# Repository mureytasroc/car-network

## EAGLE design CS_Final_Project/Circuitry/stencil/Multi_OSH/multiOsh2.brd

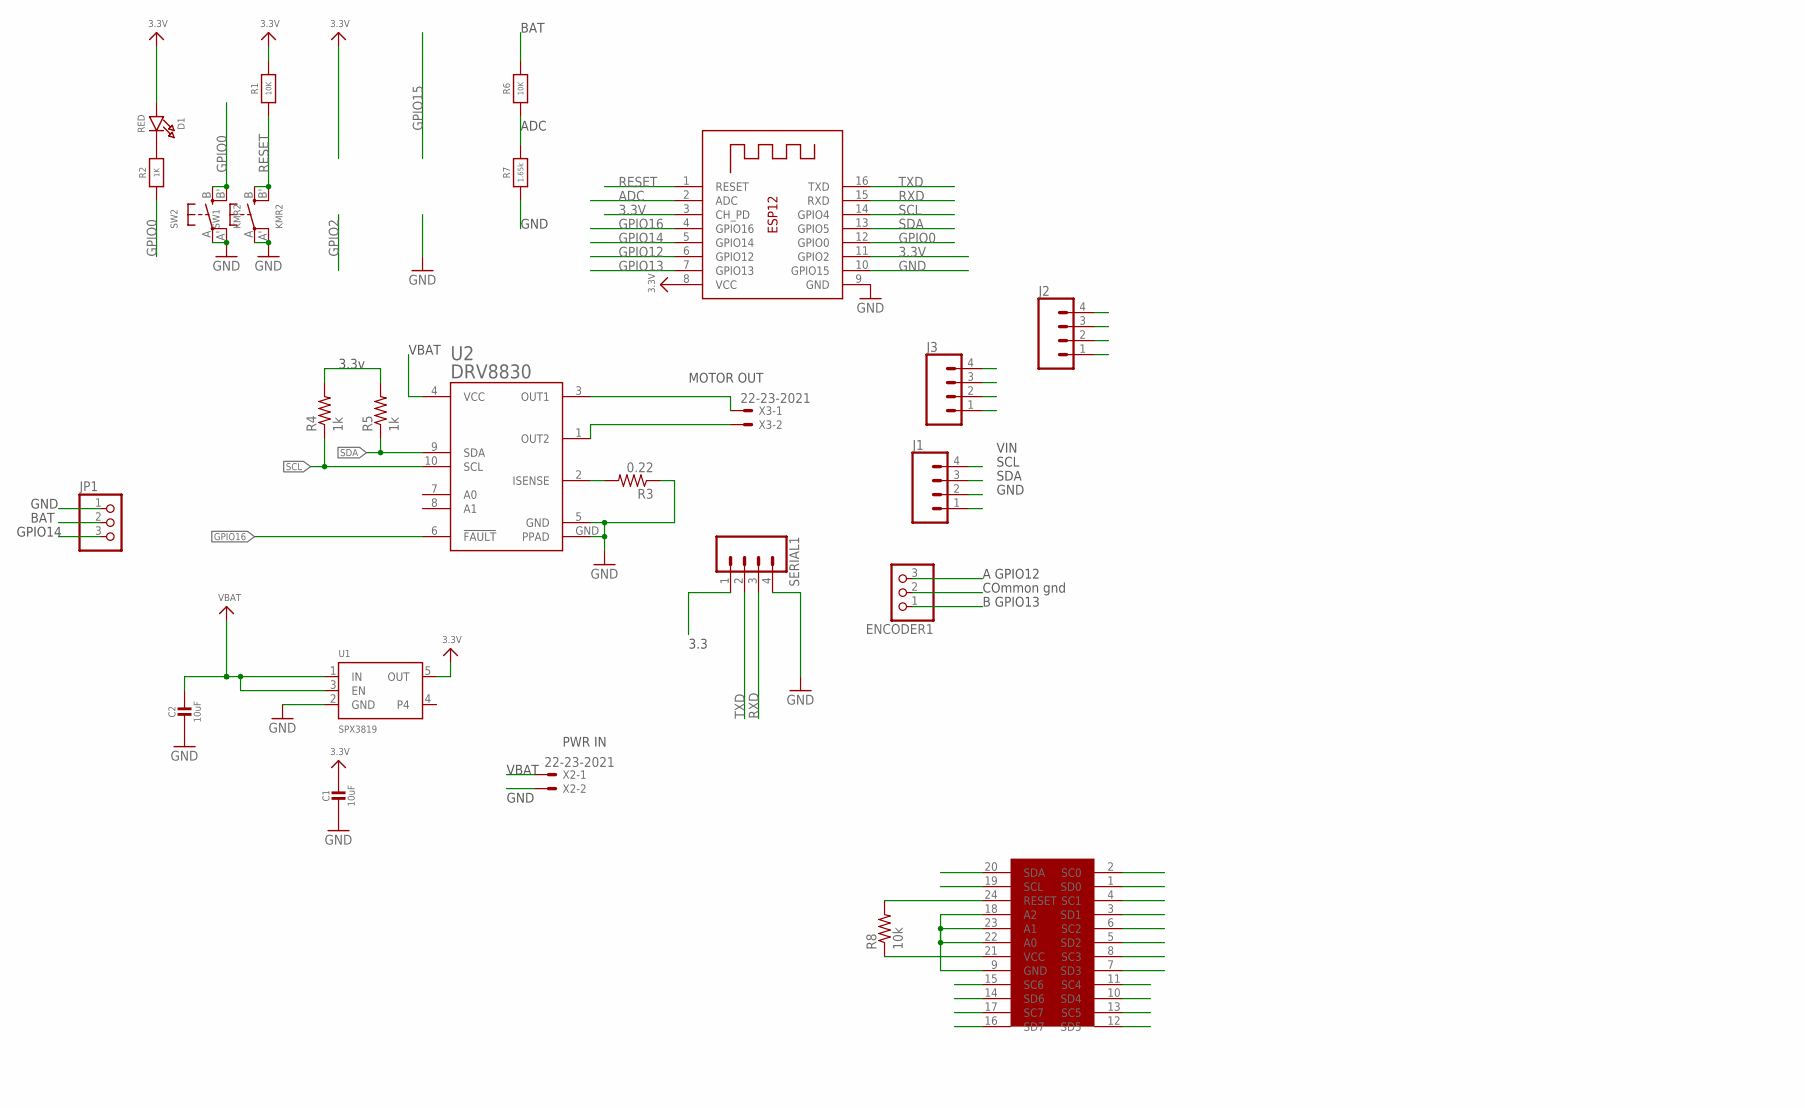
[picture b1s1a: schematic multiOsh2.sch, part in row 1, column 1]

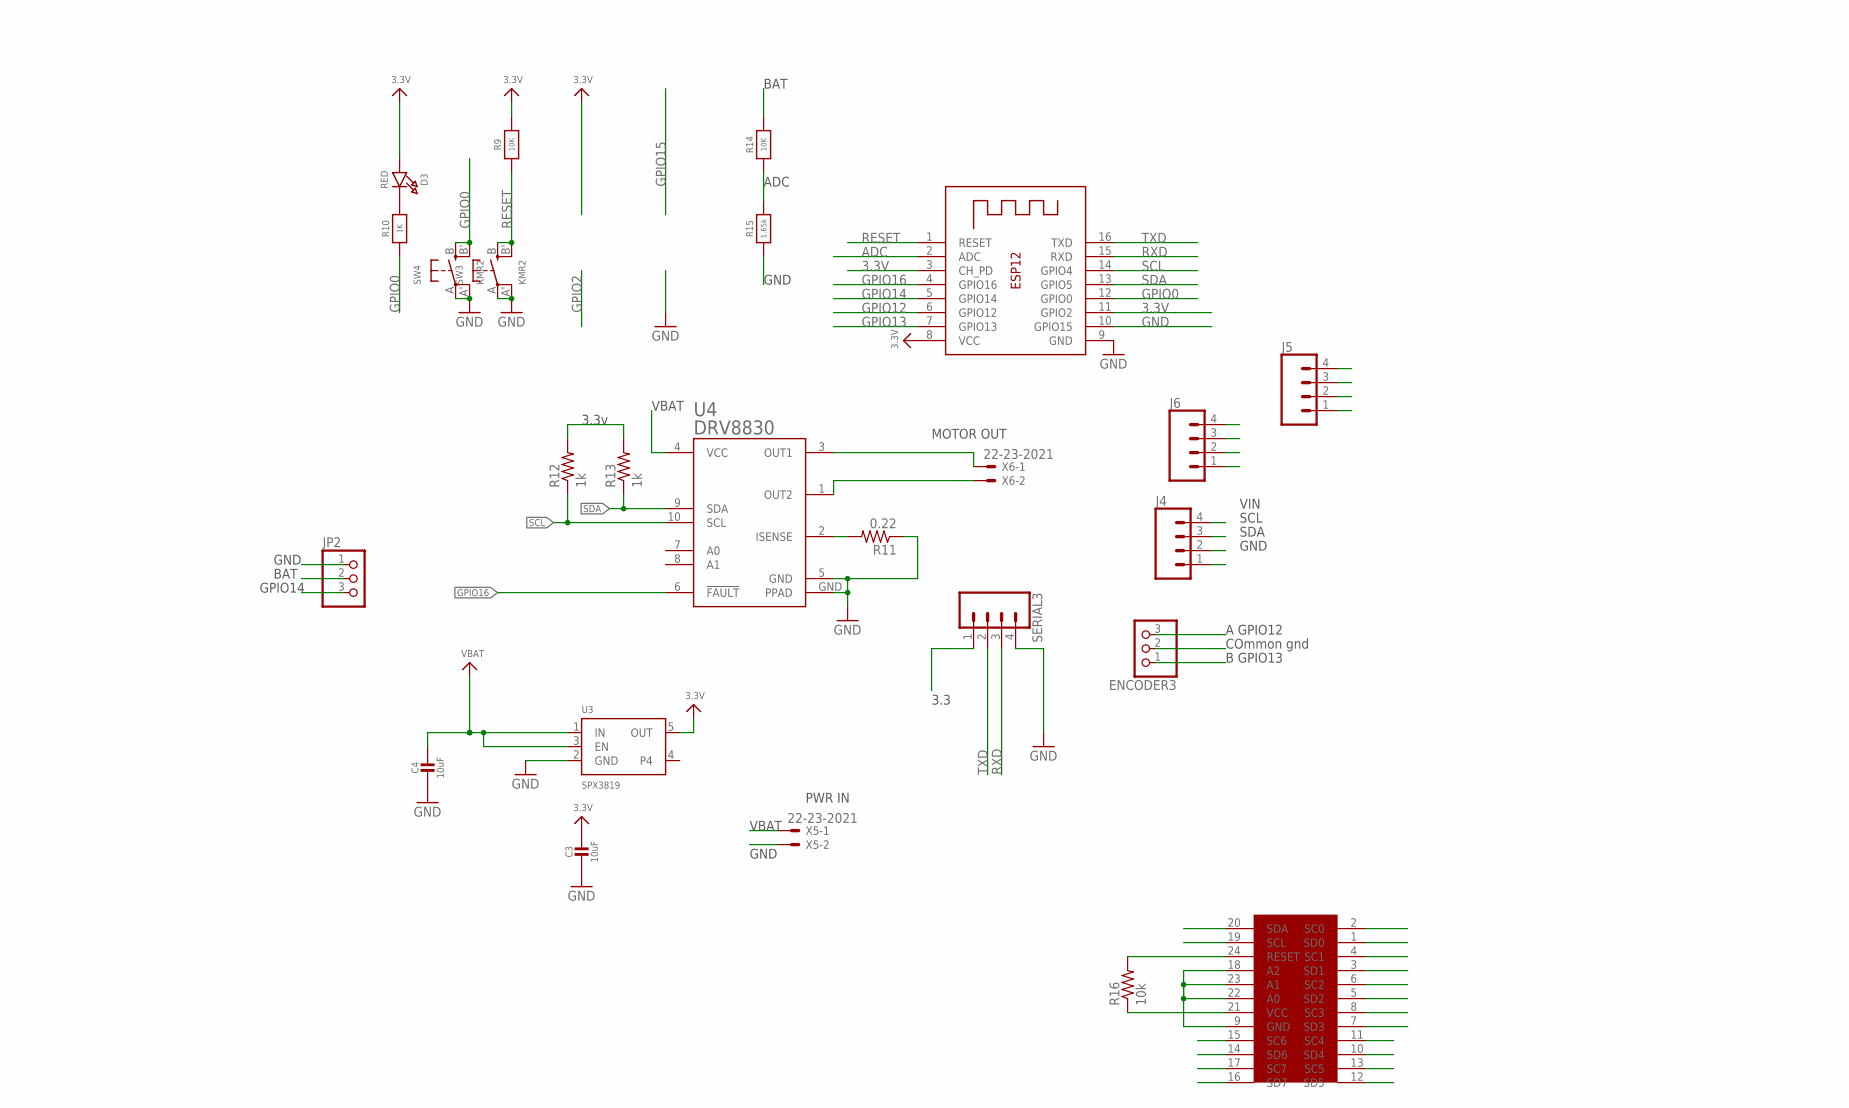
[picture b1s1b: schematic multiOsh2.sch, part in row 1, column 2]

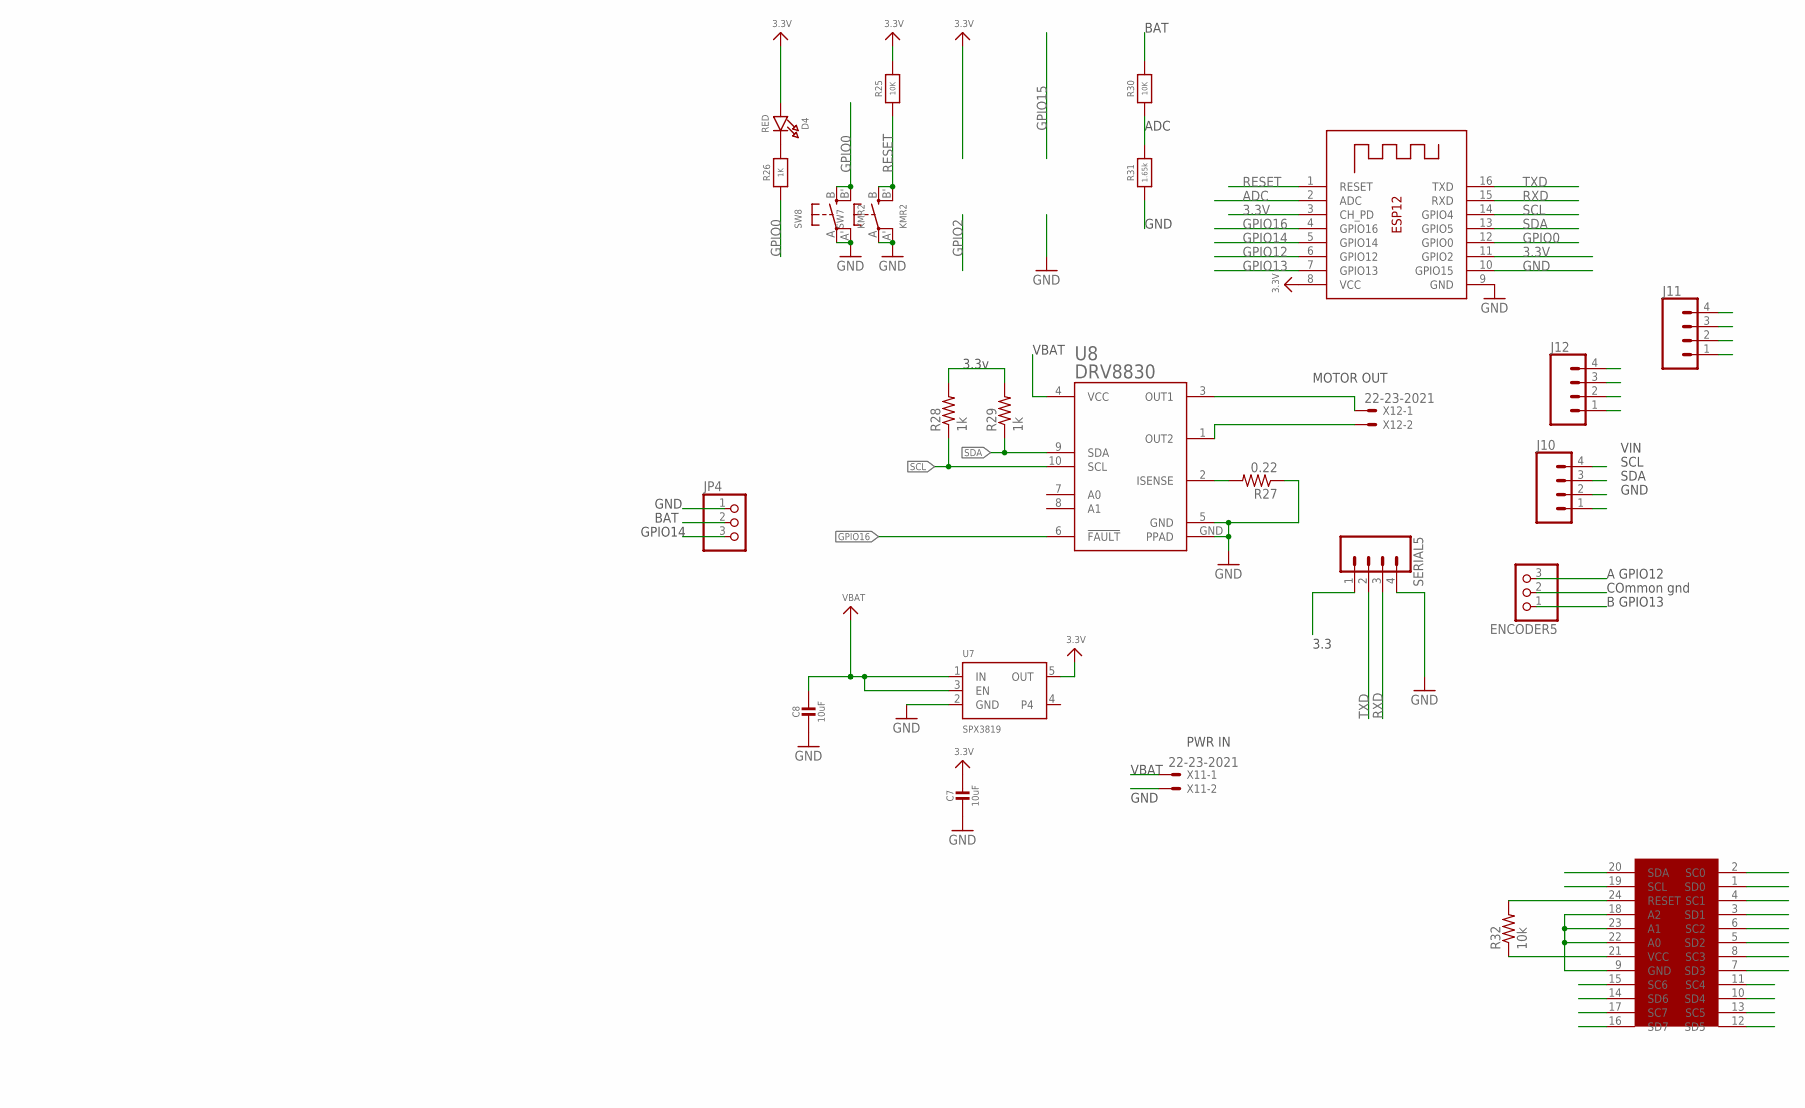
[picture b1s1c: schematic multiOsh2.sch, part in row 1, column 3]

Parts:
C1, C2, C3, C4, C7, C8: 10uF; 0805-NO
D1, D3, D4: RED; CHIPLED_0805_NOOUTLINE
ENCODER1, ENCODER3, ENCODER5: PINHD-1X3; 1X03
J1, J2, J3, J4, J5, J6, J10, J11, J12: CONN_04; 1X04
JP1, JP2, JP4: PINHD-1X3; 1X03
R1, R6, R9, R14, R25, R30: 10K; 0805-NO
R2, R10, R26: 1K; 0805-NO
R3, R11, R27: 0.22; 0805
R4, R5, R12, R13, R28, R29: 1k; R0805
R7, R15, R31: 1.65k; 0805-NO
R8, R16, R32: 10k; M0805
SERIAL1, SERIAL3, SERIAL5: CONN_04; 1X04
SW1, SW2, SW3, SW4, SW7, SW8: KMR2; BTN_KMR2_4.6X2.8
U1, U3, U7: SPX3819; SOT23-5
U2, U4, U8: DRV8830; MSOP-10-GNDPAD
U$8, U$16, U$35: TCA9548A; QFN24-4X4
X1, X4, X10: ESP-12
X2, X3, X5, X6, X11, X12: 22-23-2021

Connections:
3.3V: C1.1, C3.1, C7.1, D1.A, D3.A, D4.A, J1.4, J2.4, J3.4, J4.4, J5.4, J6.4, J10.4, J11.4, J12.4, R1.2, R4.2, R5.2, R8.1, R9.2, R12.2, R13.2, R16.1, R25.2, R28.2, R29.2, R32.1, SERIAL1.1, SERIAL3.1, SERIAL5.1, U1.5 (OUT), U3.5 (OUT), U7.5 (OUT), U$8.21 (VCC), U$16.21 (VCC), U$35.21 (VCC), X1.3 (CH_PD), X1.8 (VCC), X1.11 (GPIO2), X4.3 (CH_PD), X4.8 (VCC), X4.11 (GPIO2), X10.3 (CH_PD), X10.8 (VCC), X10.11 (GPIO2)
ADC: R6.1, R7.2, R14.1, R15.2, R30.1, R31.2, X1.2 (ADC), X4.2 (ADC), X10.2 (ADC)
GND: C1.2, C2.2, C3.2, C4.2, C7.2, C8.2, ENCODER1.2, ENCODER3.2, ENCODER5.2, J1.1, J2.1, J3.1, J4.1, J5.1, J6.1, J10.1, J11.1, J12.1, JP1.1, JP2.1, JP4.1, R3.1, R7.1, R11.1, R15.1, R27.1, R31.1, SERIAL1.4, SERIAL3.4, SERIAL5.4, SW1.A, SW1.A' (P1), SW2.A, SW2.A' (P1), SW3.A, SW3.A' (P1), SW4.A, SW4.A' (P1), SW7.A, SW7.A' (P1), SW8.A, SW8.A' (P1), U1.2 (GND), U2.5 (GND), U2.GND (PPAD), U3.2 (GND), U4.5 (GND), U4.GND (PPAD), U7.2 (GND), U8.5 (GND), U8.GND (PPAD), U$8.9 (GND), U$8.18 (A2), U$8.22 (A0), U$8.23 (A1), U$16.9 (GND), U$16.18 (A2), U$16.22 (A0), U$16.23 (A1), U$35.9 (GND), U$35.18 (A2), U$35.22 (A0), U$35.23 (A1), X1.9 (GND), X1.10 (GPIO15), X2.2, X4.9 (GND), X4.10 (GPIO15), X5.2, X10.9 (GND), X10.10 (GPIO15), X11.2
GPIO0: R2.1, R10.1, R26.1, SW2.B (S), SW2.B' (S1), SW4.B (S), SW4.B' (S1), SW8.B (S), SW8.B' (S1), X1.12 (GPIO0), X4.12 (GPIO0), X10.12 (GPIO0)
GPIO12: ENCODER1.3, ENCODER3.3, ENCODER5.3, X1.6 (GPIO12), X4.6 (GPIO12), X10.6 (GPIO12)
GPIO13: ENCODER1.1, ENCODER3.1, ENCODER5.1, X1.7 (GPIO13), X4.7 (GPIO13), X10.7 (GPIO13)
GPIO14: JP1.3, JP2.3, JP4.3, X1.5 (GPIO14), X4.5 (GPIO14), X10.5 (GPIO14)
GPIO16: U2.6 (!FAULT), U4.6 (!FAULT), U8.6 (!FAULT), X1.4 (GPIO16), X4.4 (GPIO16), X10.4 (GPIO16)
MOT1: U2.1 (OUT2), X3.2
MOT2: U2.3 (OUT1), X3.1
MOT3: U4.1 (OUT2), X6.2
MOT4: U4.3 (OUT1), X6.1
MOT7: U8.1 (OUT2), X12.2
MOT8: U8.3 (OUT1), X12.1
unnamed: D1.C, R2.2
unnamed: R3.2, U2.2 (ISENSE)
unnamed: R8.2, U$8.24 (RESET)
unnamed: D3.C, R10.2
unnamed: R11.2, U4.2 (ISENSE)
unnamed: R16.2, U$16.24 (RESET)
unnamed: D4.C, R26.2
unnamed: R27.2, U8.2 (ISENSE)
unnamed: R32.2, U$35.24 (RESET)
RESET: R1.1, R9.1, R25.1, SW1.B (S), SW1.B' (S1), SW3.B (S), SW3.B' (S1), SW7.B (S), SW7.B' (S1), X1.1 (RESET), X4.1 (RESET), X10.1 (RESET)
RXD: SERIAL1.3, SERIAL3.3, SERIAL5.3, X1.15 (RXD), X4.15 (RXD), X10.15 (RXD)
SC1: U$8.2 (SC0)
SC2: U$8.4 (SC1)
SC3: U$8.6 (SC2)
SC4: J3.2, U$8.8 (SC3)
SC5: J1.2, U$8.15 (SC6)
SC6: U$8.17 (SC7)
SC7: U$8.11 (SC4)
SC8: J2.2, U$8.13 (SC5)
SC9: U$16.2 (SC0)
SC10: U$16.4 (SC1)
SC11: U$16.6 (SC2)
SC12: J6.2, U$16.8 (SC3)
SC13: J4.2, U$16.15 (SC6)
SC14: U$16.17 (SC7)
SC15: U$16.11 (SC4)
SC24: J5.2, U$16.13 (SC5)
SC25: U$35.2 (SC0)
SC26: U$35.4 (SC1)
SC27: U$35.6 (SC2)
SC28: J12.2, U$35.8 (SC3)
SC29: J10.2, U$35.15 (SC6)
SC30: U$35.17 (SC7)
SC31: U$35.11 (SC4)
SC40: J11.2, U$35.13 (SC5)
SCL: R4.1, R12.1, R28.1, U2.10 (SCL), U4.10 (SCL), U8.10 (SCL), U$8.19 (SCL), U$16.19 (SCL), U$35.19 (SCL), X1.14 (GPIO4), X4.14 (GPIO4), X10.14 (GPIO4)
SD1: U$8.1 (SD0)
SD2: U$8.3 (SD1)
SD3: U$8.5 (SD2)
SD4: J3.3, U$8.7 (SD3)
SD5: J1.3, U$8.14 (SD6)
SD6: U$8.16 (SD7)
SD7: U$8.10 (SD4)
SD8: J2.3, U$8.12 (SD5)
SD9: U$16.1 (SD0)
SD10: U$16.3 (SD1)
SD11: U$16.5 (SD2)
SD12: J6.3, U$16.7 (SD3)
SD13: J4.3, U$16.14 (SD6)
SD14: U$16.16 (SD7)
SD15: U$16.10 (SD4)
SD24: J5.3, U$16.12 (SD5)
SD25: U$35.1 (SD0)
SD26: U$35.3 (SD1)
SD27: U$35.5 (SD2)
SD28: J12.3, U$35.7 (SD3)
SD29: J10.3, U$35.14 (SD6)
SD30: U$35.16 (SD7)
SD31: U$35.10 (SD4)
SD40: J11.3, U$35.12 (SD5)
SDA: R5.1, R13.1, R29.1, U2.9 (SDA), U4.9 (SDA), U8.9 (SDA), U$8.20 (SDA), U$16.20 (SDA), U$35.20 (SDA), X1.13 (GPIO5), X4.13 (GPIO5), X10.13 (GPIO5)
TXD: SERIAL1.2, SERIAL3.2, SERIAL5.2, X1.16 (TXD), X4.16 (TXD), X10.16 (TXD)
VBAT: C2.1, C4.1, C8.1, JP1.2, JP2.2, JP4.2, R6.2, R14.2, R30.2, U1.1 (IN), U1.3 (EN), U2.4 (VCC), U3.1 (IN), U3.3 (EN), U4.4 (VCC), U7.1 (IN), U7.3 (EN), U8.4 (VCC), X2.1, X5.1, X11.1

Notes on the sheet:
3.3v
VBAT
BAT
GND
ADC
PWR IN
MOTOR OUT
GPIO14
VIN
SCL
SDA
COmmon gnd
A GPIO12
B GPIO13
3.3

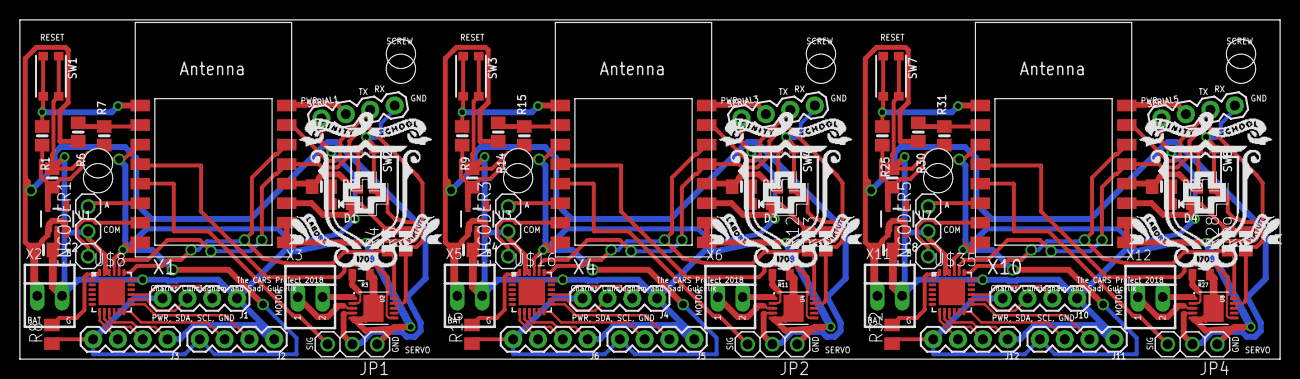
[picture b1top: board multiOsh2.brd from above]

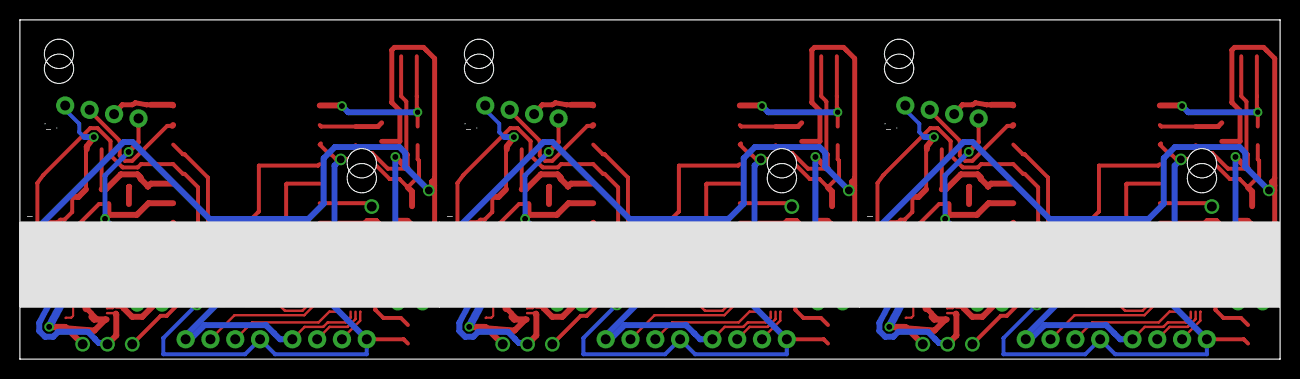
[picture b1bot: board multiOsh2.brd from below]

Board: 2 copper layers, 129.0 x 34.7 mm, 84 parts (6 on the bottom side), 47 nets.

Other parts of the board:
U$36, U$39, U$42: HUZZAHLOGO
U$37, U$40, U$43: ADAFRUIT_TEXT_20MM
U$38, U$41, U$44: TRIN

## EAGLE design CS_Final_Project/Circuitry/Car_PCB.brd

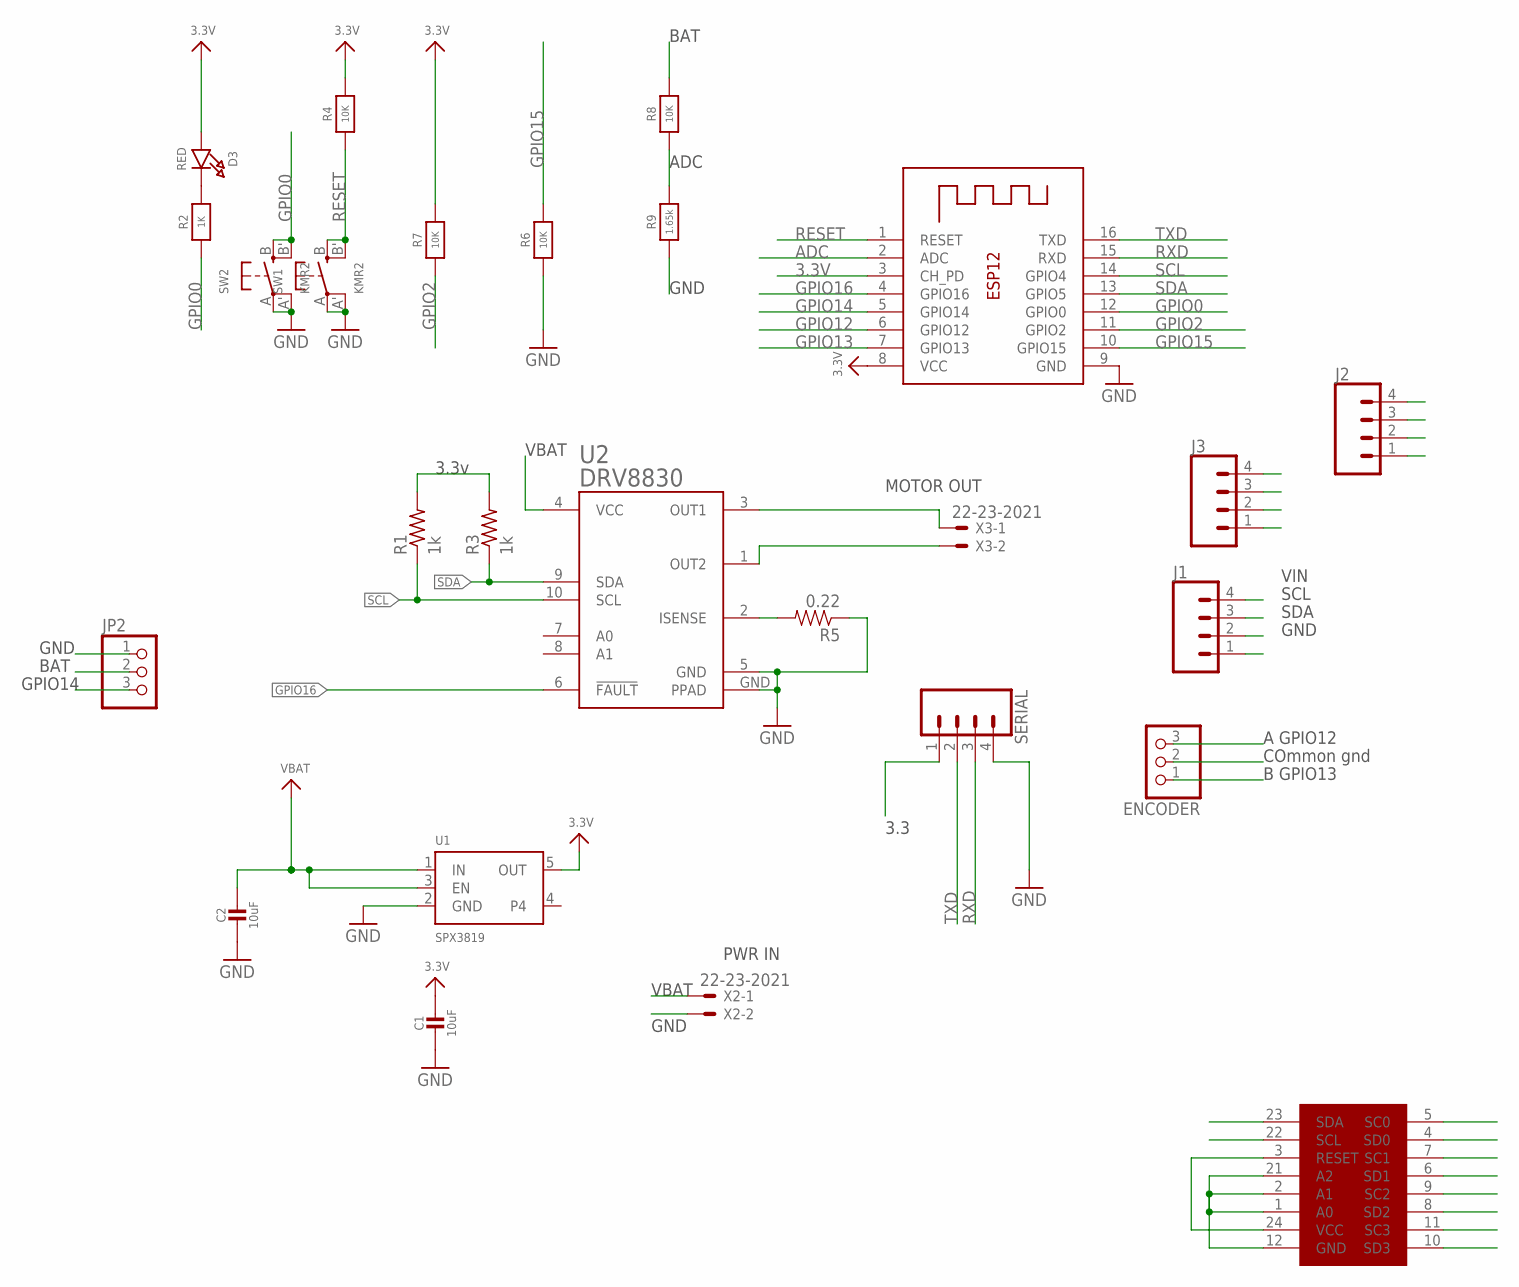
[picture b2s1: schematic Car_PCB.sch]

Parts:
C1, C2: 10uF; 0805-NO
D3: RED; CHIPLED_0805_NOOUTLINE
ENCODER: PINHD-1X3; 1X03
J1, J2, J3: CONN_04; 1X04
JP2: PINHD-1X3; 1X03
R1, R3: 1k; R0805
R2: 1K; 0805-NO
R4, R6, R7, R8: 10K; 0805-NO
R5: 0.22; 0805
R9: 1.65k; 0805-NO
SERIAL: CONN_04; 1X04
SW1, SW2: KMR2; BTN_KMR2_4.6X2.8
U1: SPX3819; SOT23-5
U2: DRV8830; MSOP-10-GNDPAD
U$1: TCA9548A; QFN24-4X4
X1: ESP-12
X2, X3: 22-23-2021

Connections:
3.3V: C1.1, D3.A, J1.4, J2.4, J3.4, R1.2, R3.2, R4.2, R7.2, SERIAL.1, U1.5 (OUT), U$1.3 (RESET), U$1.24 (VCC), X1.3 (CH_PD), X1.8 (VCC)
ADC: R8.1, R9.2, X1.2 (ADC)
GND: C1.2, C2.2, ENCODER.2, J1.1, J2.1, J3.1, JP2.1, R5.1, R6.1, R9.1, SERIAL.4, SW1.A, SW1.A' (P1), SW2.A, SW2.A' (P1), U1.2 (GND), U2.5 (GND), U2.GND (PPAD), U$1.1 (A0), U$1.2 (A1), U$1.12 (GND), U$1.21 (A2), X1.9 (GND), X2.2
GPIO0: R2.1, SW2.B (S), SW2.B' (S1), X1.12 (GPIO0)
GPIO2: R7.1, X1.11 (GPIO2)
GPIO12: ENCODER.3, X1.6 (GPIO12)
GPIO13: ENCODER.1, X1.7 (GPIO13)
GPIO14: JP2.3, X1.5 (GPIO14)
GPIO15: R6.2, X1.10 (GPIO15)
GPIO16: U2.6 (!FAULT), X1.4 (GPIO16)
MOT1: U2.3 (OUT1), X3.1
MOT2: U2.1 (OUT2), X3.2
unnamed: D3.C, R2.2
unnamed: R5.2, U2.2 (ISENSE)
RESET: R4.1, SW1.B (S), SW1.B' (S1), X1.1 (RESET)
RXD: SERIAL.3, X1.15 (RXD)
SC0: J1.3, U$1.5 (SC0)
SC1: J2.3, U$1.7 (SC1)
SC2: U$1.9 (SC2)
SC3: J3.3, U$1.11 (SC3)
SCL: R1.1, U2.10 (SCL), U$1.22 (SCL), X1.14 (GPIO4)
SD0: J1.2, U$1.4 (SD0)
SD1: J2.2, U$1.6 (SD1)
SD2: U$1.8 (SD2)
SD3: J3.2, U$1.10 (SD3)
SDA: R3.1, U2.9 (SDA), U$1.23 (SDA), X1.13 (GPIO5)
TXD: SERIAL.2, X1.16 (TXD)
VBAT: C2.1, JP2.2, R8.2, U1.1 (IN), U1.3 (EN), U2.4 (VCC), X2.1

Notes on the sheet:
3.3v
VBAT
BAT
GND
ADC
PWR IN
MOTOR OUT
GPIO14
VIN
SCL
SDA
COmmon gnd
A GPIO12
B GPIO13
3.3

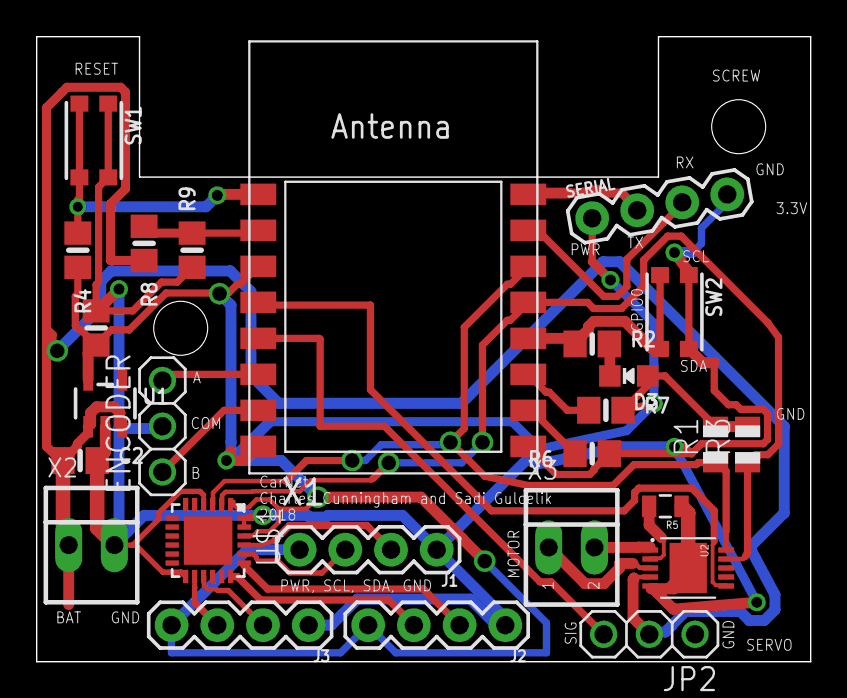
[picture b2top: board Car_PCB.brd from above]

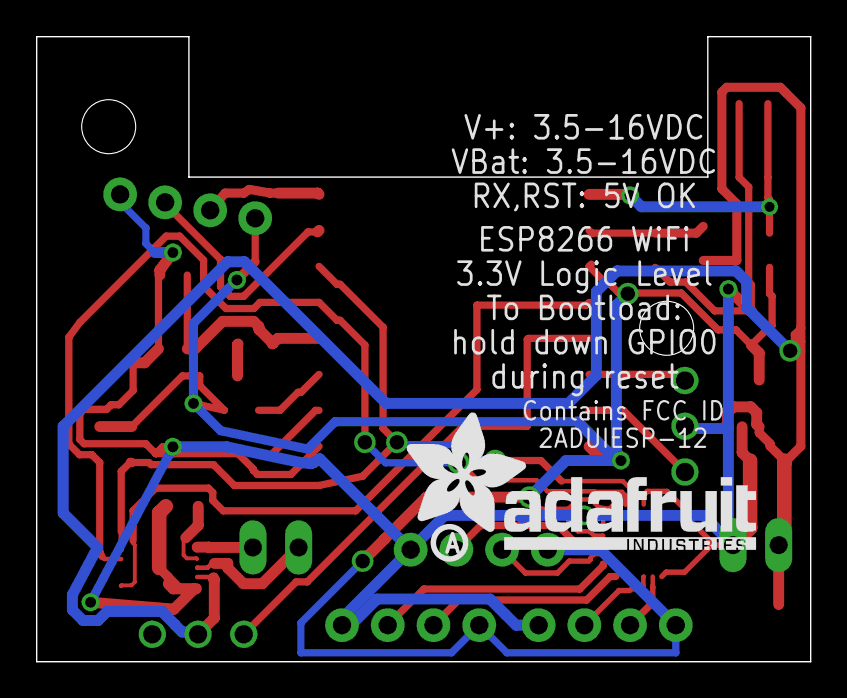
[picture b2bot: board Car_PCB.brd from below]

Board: 2 copper layers, 43.0 x 34.7 mm, 29 parts (3 on the bottom side), 26 nets.

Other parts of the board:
U$2: HUZZAHLOGO
U$12: ADAFRUIT_TEXT_20MM
U$13: PCBFEAT-REV-040

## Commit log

2018-04-25 init
2018-05-17 Revert "Merge branch 'master' of https://github.com/mureytasroc/CarNetwork"
    This reverts commit a45a0045a92c6dc43e66f74dc99afbd22e46fa88, reversing
    changes made to 7d7a9c1b56f2fe83920f8a54f55361a334df6815.
2018-05-22 now?
2018-05-24 trying
2018-05-31 kaka
2018-06-04 midFixing
2018-06-04 fsadjk
2018-06-04 adfs
2018-06-04 final edits for a bit
2018-06-05 fdsa
2018-06-05 almostDeBugged
2018-06-05 ITISBEINGIMPLEMENTED
2018-06-05 sadf
2018-06-05 asdf
2018-06-05 dfas
2018-06-05 ItCompilesButIdkWtfIsGoingOn
2018-06-06 doesItWork???
2018-06-06 arrrgghhhhh
2018-06-06 aqzswxdec
2018-06-06 infiniteLoopError
2018-06-06 asdfasdfafsd
2018-06-06 PUUUUSHHHH
2018-06-06 whyDoesItNotWork
2018-06-06 Teleportation
2018-06-06 as;dkasdf;;asfddfsa;adfsadfs;fsadasdfjklafdsjkadfjksk;adfsjsdfa;sadf;
2018-06-06 still#$%^^&***&%
2018-06-07 asffsd
2018-06-07 safdas
2018-06-07 dsaf
2018-06-07 hljkhkl
2018-06-07 gahhhhhhhhhhh!@#$%^%$#@!~!@#$%^%$#@!@#$%^%$#@!@#$%^%$#@!@#$%^%$#@!@#$%$#@#$%$#@#$%$#@!@#$%^$#@#$%^$#@#$%$#@#$%
2018-06-09 master
2018-06-10 T^&BBT^&*B^*&%^R&
2018-06-13 R*%UBNIN
2018-06-13 Revert "a"
    This reverts commit 0ea7e428ac573384afb96676350230cbd42f0eb4.
2018-06-13 Revert "R*%UBNIN"
    This reverts commit 1c2c4b22cea6128684b4be3c85eba9b46d263418.
2018-06-13 Revert "Revert "R*%UBNIN""
    This reverts commit 9cf39a6a1837bb21f0977229fe0c6344483a6f06.
2018-06-13 prakata
2018-06-13 Revert "m"
    This reverts commit 2f721b070915a0c6e64a1e2351bcc087f2a0364c.
2018-06-13 revert
2018-06-13 Revert "fdsa"
    This reverts commit 60add33f88e891808d7423621e5aaa4d47b19a9a.
2018-06-14 Revert "v"
    This reverts commit 7ead5e88b0f2380e4285c9c24e80ec21ea90fb63.
2018-06-15 test
2018-06-16 Doesn't_work_yet

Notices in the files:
parts and their libraries:
microbuilder: This work is placed in the public domain, and may be freely used for commercial and non-commercial work with the following conditions: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
SparkFun-Resistors: Licensing: CC v3.0 Share-Alike You are welcome to use this library for commercial purposes.
si70xx-10: (c) 2014 Samuel Lourenço
